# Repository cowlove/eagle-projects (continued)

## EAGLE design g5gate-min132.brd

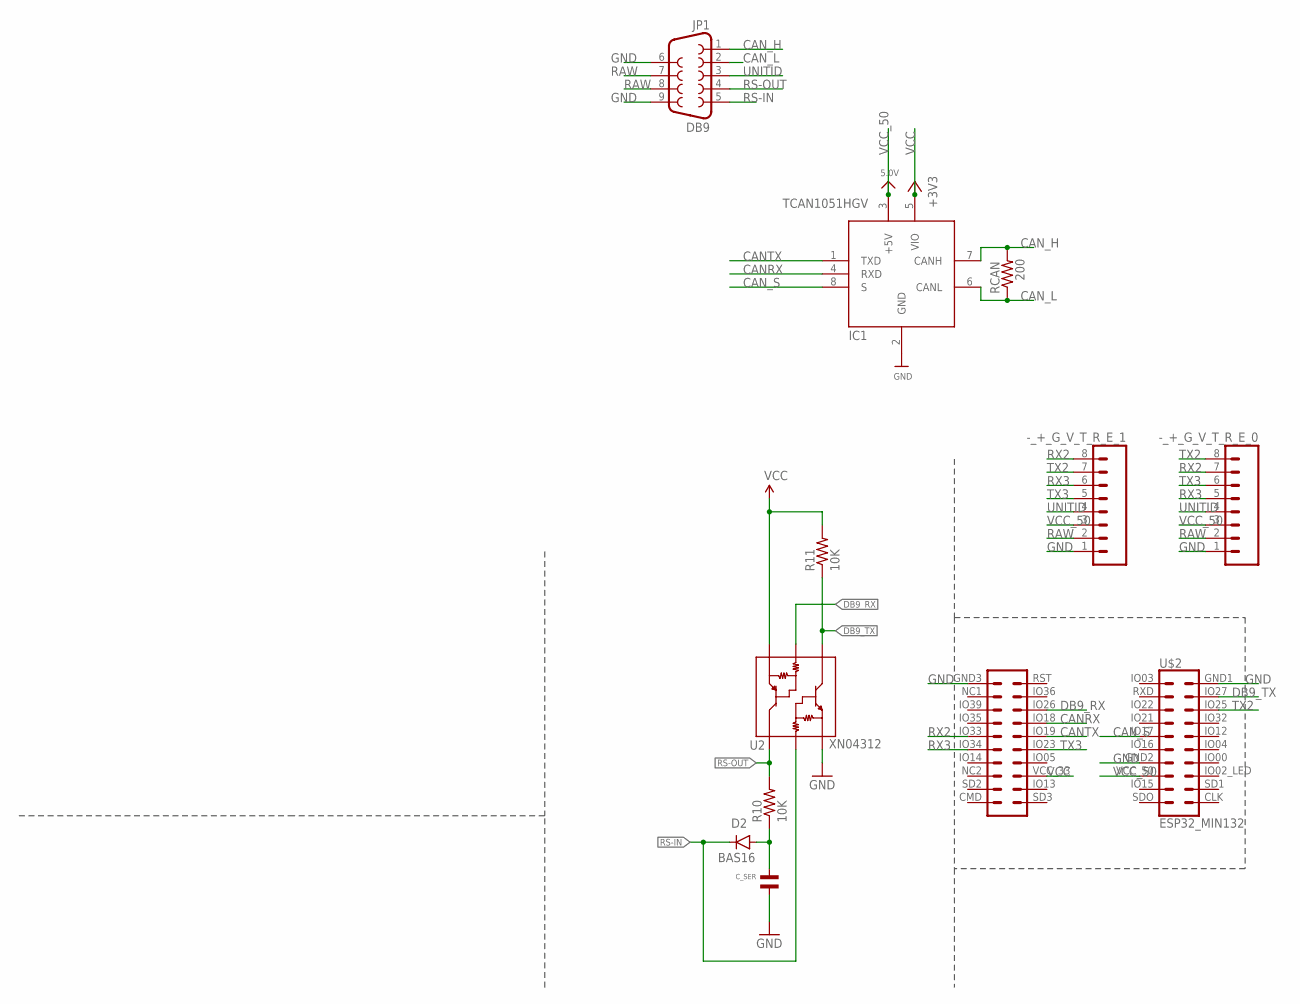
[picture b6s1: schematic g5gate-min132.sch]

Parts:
-_+_G_V_T_R_E_0, -_+_G_V_T_R_E_1: MF-CON-2.54mm-01x08; 1X08
C_SER: CAPACITOR_NP_0603; C0603
D2: BAS16; SOD-323
IC1: TCAN1051HGV; SOIC8_150MIL
JP1: DB9
R10, R11: 10K; 0603-RES
RCAN: 200; 0603-RES
U2: XN04312; SOT23-6
U$2: ESP32_MIN132

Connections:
CANRX: IC1.4 (RXD), U$2.IO18 (8)
CANTX: IC1.1 (TXD), U$2.IO19 (10)
CAN_H: IC1.7 (CANH), JP1.1, RCAN.2
CAN_L: IC1.6 (CANL), JP1.2, RCAN.1
CAN_S: IC1.8 (S), U$2.IO17 (29)
DB9_RX: U2.2 (B2), U$2.IO26 (6)
DB9_TX: R11.1, U2.1 (C1), U$2.IO27 (24)
GND: -_+_G_V_T_R_E_0.1, -_+_G_V_T_R_E_1.1, C_SER.P$2, IC1.2 (GND), JP1.6, JP1.9, U2.6 (E1), U$2.GND1 (22), U$2.GND2 (33), U$2.GND3 (1)
unnamed: C_SER.P$1, D2.A, R10.1
RAW: -_+_G_V_T_R_E_0.2, -_+_G_V_T_R_E_1.2, JP1.7, JP1.8
RS-IN: D2.C, JP1.5, U2.5 (B1)
RS-OUT: JP1.4, R10.2, U2.4 (C2)
RX2: -_+_G_V_T_R_E_0.7, -_+_G_V_T_R_E_1.8, U$2.IO33 (9)
RX3: -_+_G_V_T_R_E_0.5, -_+_G_V_T_R_E_1.6, U$2.IO34 (11)
TX2: -_+_G_V_T_R_E_0.8, -_+_G_V_T_R_E_1.7, U$2.IO25 (26)
TX3: -_+_G_V_T_R_E_0.6, -_+_G_V_T_R_E_1.5, U$2.IO23 (12)
UNITID: -_+_G_V_T_R_E_0.4, -_+_G_V_T_R_E_1.4, JP1.3
VCC: IC1.5 (VIO), R11.2, U2.3 (E2), U$2.VCC_33 (16)
VCC_50: -_+_G_V_T_R_E_0.3, -_+_G_V_T_R_E_1.3, IC1.3 (+5V), U$2.VCC_50 (35)

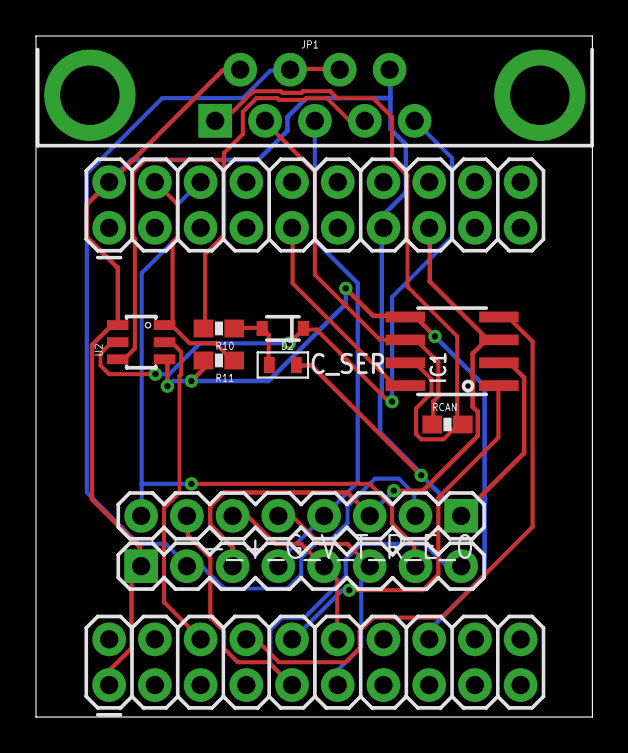
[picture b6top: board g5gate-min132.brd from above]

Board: 2 copper layers, 30.9 x 37.8 mm, 11 parts (0 on the bottom side), 19 nets.

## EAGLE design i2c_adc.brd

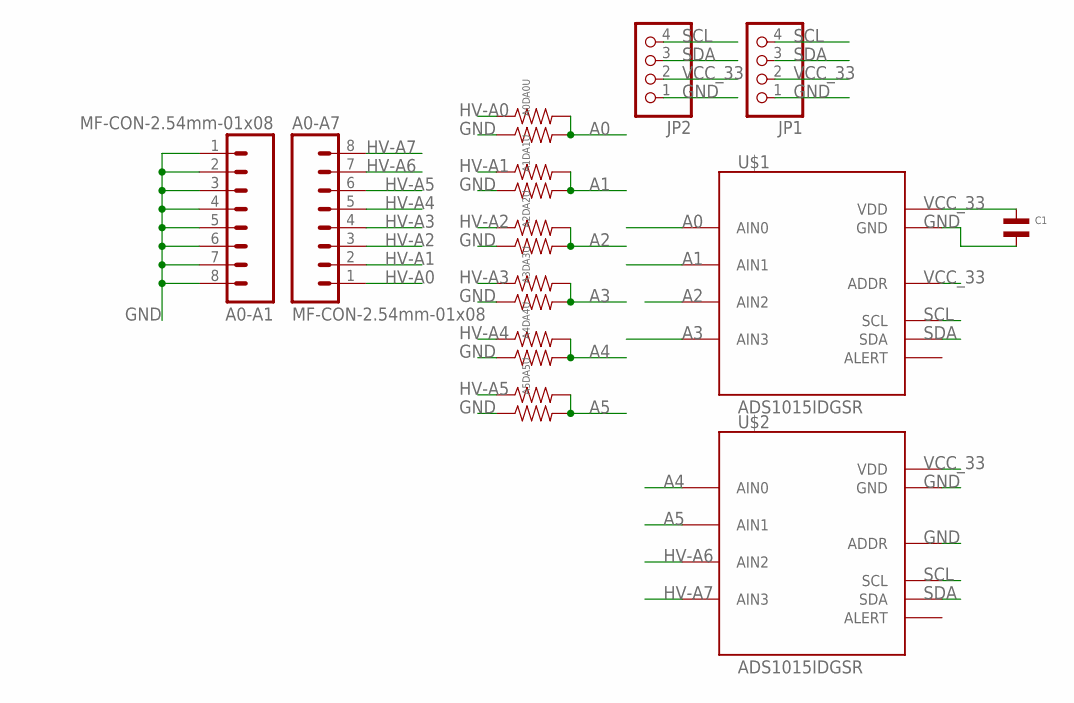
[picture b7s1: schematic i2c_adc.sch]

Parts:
A0-A1, A0-A7: MF-CON-2.54mm-01x08; 1X08
A0D, A0U, A1D, A1U, A2D, A2U, A3D, A3U, A4D, A4U, A5D, A5U: RESISTOR_0603; R0603
C1: CAPACITOR_NP_1206; C1206
JP1, JP2: HEADER-1X41MMPADS; 1X04_1.0MM
U$1, U$2: ADS1015IDGSR; MSOP10_0.5

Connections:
A0: A0D.P$2, A0U.P$2, U$1.4 (AIN0)
A1: A1D.P$2, A1U.P$2, U$1.5 (AIN1)
A2: A2D.P$2, A2U.P$2, U$1.6 (AIN2)
A3: A3D.P$2, A3U.P$2, U$1.7 (AIN3)
A4: A4D.P$2, A4U.P$2, U$2.4 (AIN0)
A5: A5D.P$2, A5U.P$2, U$2.5 (AIN1)
GND: A0-A1.1, A0-A1.2, A0-A1.3, A0-A1.4, A0-A1.5, A0-A1.6, A0-A1.7, A0-A1.8, A0D.P$1, A1D.P$1, A2D.P$1, A3D.P$1, A4D.P$1, A5D.P$1, C1.P$2, JP1.1, JP2.1, U$1.3 (GND), U$2.1 (ADDR), U$2.3 (GND)
HV-A0: A0-A7.1, A0U.P$1
HV-A1: A0-A7.2, A1U.P$1
HV-A2: A0-A7.3, A2U.P$1
HV-A3: A0-A7.4, A3U.P$1
HV-A4: A0-A7.5, A4U.P$1
HV-A5: A0-A7.6, A5U.P$1
HV-A6: A0-A7.7, U$2.6 (AIN2)
HV-A7: A0-A7.8, U$2.7 (AIN3)
SCL: JP1.4, JP2.4, U$1.10 (SCL), U$2.10 (SCL)
SDA: JP1.3, JP2.3, U$1.9 (SDA), U$2.9 (SDA)
VCC_33: C1.P$1, JP1.2, JP2.2, U$1.1 (ADDR), U$1.8 (VDD), U$2.8 (VDD)

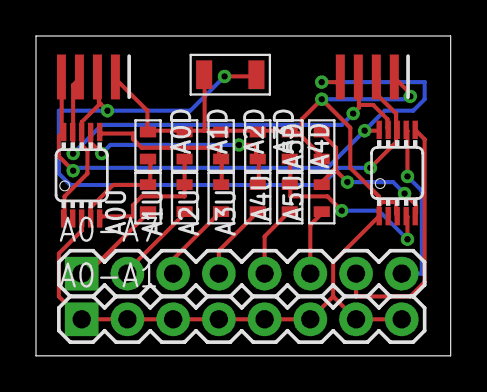
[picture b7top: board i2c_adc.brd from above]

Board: 2 copper layers, 23.0 x 17.8 mm, 19 parts (0 on the bottom side), 18 nets.
